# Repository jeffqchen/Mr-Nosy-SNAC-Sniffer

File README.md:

# Mr Nosy SNAC Sniffer

”Mr. Nosy“” SNAC Sniffer is a hardware iteration that's powered by the [RetroSpy](https://github.com/retrospy/RetroSpy).

I've created three versions. The long with the impression of an inline design. The square can be set up to hide the wires behind it. The "L" is a shorter & more compact design of the long.

-------------
## Parts

- Arduino Nano - [Link](https://github.com/jeffqchen/JeffParts/blob/main/Board/Arduino/Nano/info.md)

- HDMI Female Socket, Through Hole - [Link](https://github.com/jeffqchen/JeffParts/blob/main/Connectors/HDMI/Female/PCB/info.md)

- 2.54mm-Pitched Pin Header, Straight - [Link](https://github.com/jeffqchen/JeffParts/blob/main/Connectors/Pin%20Header/2.54mm%20Pitch/Male%20Straight/info.md)

- 2x15 Socket, 2.54mm-pitched, 0.6" Row Spacing (Optional)

- Jumper Caps

- "Mr. Nosy" PCB
  - Long Version: https://oshpark.com/shared_projects/CRrWdsM4
  - Square Version: https://oshpark.com/shared_projects/UYfhPj0N
  - L Version: https://oshpark.com/shared_projects/WcJKoEXY

-------------

## Assembly

Assembly is pretty straight forward. Parts belong to the side with silkscreen printings.

Note on the long version, the two HDMI headers are on different sides. Remember to solder the jumper headers before soldering the Arduino or its socket, otherwise it will be kind of hard to do afterwards.

-------------
## Special Thanks

@40wattRange
- https://twitter.com/40wattrange

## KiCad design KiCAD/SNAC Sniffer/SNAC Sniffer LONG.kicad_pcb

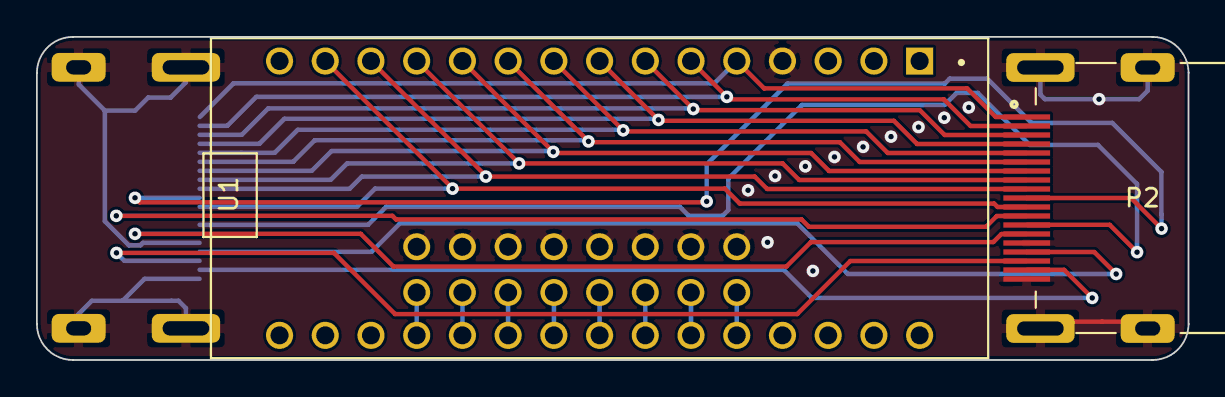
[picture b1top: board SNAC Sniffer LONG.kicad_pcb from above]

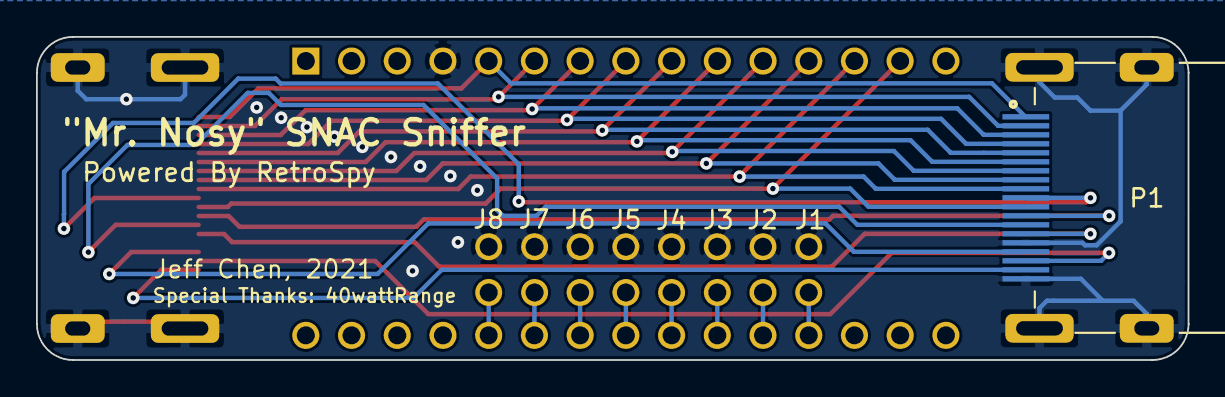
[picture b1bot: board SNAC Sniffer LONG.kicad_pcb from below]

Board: 2 copper layers, 64.0 x 18.0 mm, 11 parts (6 on the bottom side), 26 nets.

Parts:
J1, J2, J3, J4, J5, J6, J7, J8: PinHeader; Pin_Header_2.54
P1, P2: HDMI_Female
U1: Arduino_Nano

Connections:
GND: J1.2, J2.2, J3.2, J4.2, J5.2, J6.2, J7.2, J8.2, P1.15, P1.19, P1.S1, P1.S2, P1.S3, P1.S4, P2.15, P2.19, P2.S1, P2.S2, P2.S3, P2.S4, U1.4
unnamed: J1.1, U1.19
unnamed: J2.1, U1.20
unnamed: J3.1, U1.21
unnamed: J4.1, U1.22
unnamed: J5.1, U1.23
unnamed: J6.1, U1.24
unnamed: J7.1, U1.25
unnamed: J8.1, U1.26
unnamed: P1.1, P2.1, U1.5
unnamed: P1.2, P2.2, U1.6
unnamed: P1.3, P2.3, U1.7
unnamed: P1.4, P2.4, U1.8
unnamed: P1.5, P2.5, U1.9
unnamed: P1.6, P2.6, U1.10
unnamed: P1.7, P2.7, U1.11
unnamed: P1.8, P2.8, U1.12
unnamed: P1.9, P2.9, U1.13
unnamed: P1.10, P2.10
unnamed: P1.11, P2.11, U1.14
unnamed: P1.12, P2.12
unnamed: P1.13, P2.13
unnamed: P1.14, P2.14
unnamed: P1.16, P2.16
unnamed: P1.17, P2.17
unnamed: P1.18, P2.18

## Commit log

2021-11-29 KiCAD files
2021-11-29 Write Readme
2021-11-29 Update KiCAD files
2021-11-30 add ver.L
